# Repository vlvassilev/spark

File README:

spark-relay-actuator-pi is a hardware platform for managed power
distribution based on the Spark hardware platform
for networking. Both are developed by
Lightside Instruments AS.

The project includes schematic and PCB
design files for KiCAD and technical documentation for
production of a 19 inch rack mountable ESD Acrylic box.

The project is published by Lightside Instruments AS
under TAPR Open Hardware License. Read the LICENSE file
for details.

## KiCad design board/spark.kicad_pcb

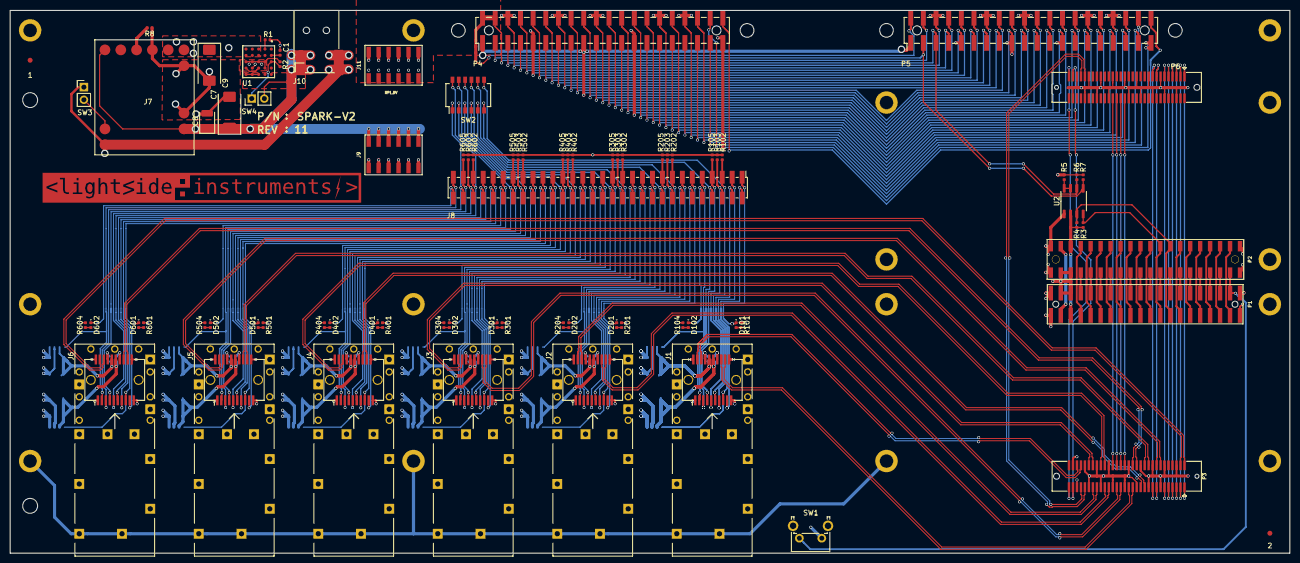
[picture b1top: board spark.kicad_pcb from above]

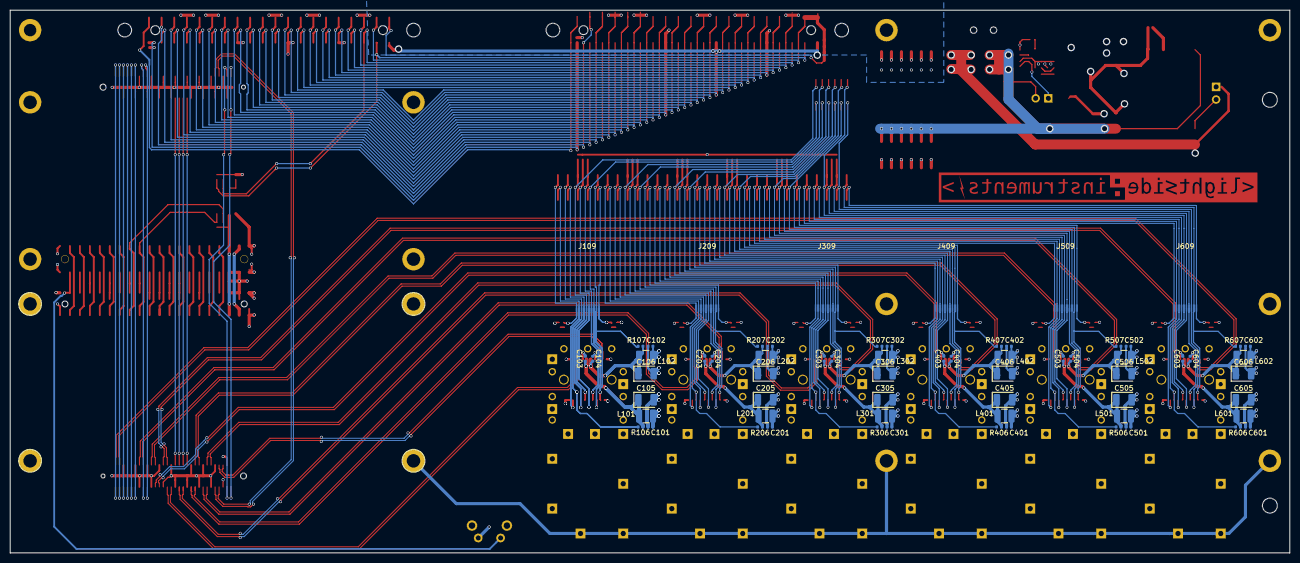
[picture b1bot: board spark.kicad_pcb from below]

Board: 4 copper layers, 257.0 x 109.0 mm, 145 parts (66 on the bottom side), 198 nets.

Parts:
1, 2: Fiducial_1mm_Mask3mm
C1: C; C_0402_1005Metric
C7: 330uF; CP_EIA-7343-31_Kemet-D
C8, C105, C106, C205, C206, C305, C306, C405, C406, C505, C506, C605, C606: 22uF; CP_EIA-3528-21_Kemet-B
C9: 220uF; CP_EIA-7343-31_Kemet-D
C101, C102, C103, C104, C201, C202, C203, C204, C301, C302, C303, C304, C401, C402, C403, C404, C501, C502, C503, C504, C601, C602, C603, C604: 100nF; C_0402_1005Metric
D101, D201, D301, D401, D501, D601: ADM_LED; LED_0402_1005Metric
D102, D202, D302, D402, D502, D602: ALARM_LED; LED_0402_1005Metric
J1, J2, J3, J4, J5, J6: SFP+; molex-sfp-plus-747540-101
J7: PTH08T221W; R-PDSS-B11
J8: Conn_02x30_Odd_Even; PinHeader_2x30_P2.00mm_Vertical_SMD
J9, J11: Conn_02x06_Odd_Even; Socket_Strip_SMD_2x6_Pitch2mm
J10: Barrel_Jack; PJ1-021-SMT-TR
J109, J209, J309, J409, J509, J609: Conn_01x10; sfp_header
L101, L102, L201, L202, L301, L302, L401, L402, L501, L502, L601, L602: 4.7uH; L_1210_3225Metric
P1: CONN_02X20; Pin_Header_SMD_2x20_Pitch2mm
P2: Conn_02x20_Odd_Even; Socket_Strip_SMD_2x20_Pitch2mm_Alignment_Pin
P3: CONN_02X30; 61083-063400LF
P4, P5: Conn_02x20_Odd_Even; PinSocket_2x20_P2.54mm_Vertical_Inverted_SMD_Alignment_Pin
P6: CONN_02X30; 5177983-2
R1: 13K3; C_0402_1005Metric
R2: 10K; C_0402_1005Metric
R3, R4, R6, R7: 4K7; R_0402_1005Metric
R5: 200K; R_0402_1005Metric
R8: 1K21; R_0402_1005Metric
R101, R104, R201, R204, R301, R304, R401, R404, R501, R504, R601, R604: 1K; R_0402_1005Metric
R102, R103, R105, R106, R107, R202, R203, R205, R206, R207, R302, R303, R305, R306, R307, R402, R403, R405, R406, R407, R502, R503, R505, R506, R507, R602, R603, R605, R606, R607: 10K; R_0402_1005Metric
SW1: SW_Push; SW_Tactile_SPST_Angled_PTS645Vx83-2LFS
SW2: SW_DIP_x06; SW_DIP_SPSTx06_Slide_Omron_A6H-6101_W6.15mm_P1.27mm
SW3, SW4: SW_DIP_x01; PinHeader_1x02_P2.54mm_Vertical
U1: LTM4624IYPBF; Analog_Devices_Inc-BGA-0-05-08-1905_Rev_C-0
U2: PCA9306; SO-8_3.9x4.9mm_P1.27mm

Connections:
+1V8: P1.35, P2.35, R3.1, R4.1, U2.2
+3V3: C9.1, C101.1, C102.1, C201.1, C202.1, C301.1, C302.1, C401.1, C402.1, C501.1, C502.1, C601.1, C602.1, J7.5, J7.6, L101.1, L102.1, L201.1, L202.1, L301.1, L302.1, L401.1, L402.1, L501.1, L502.1, L601.1, L602.1, P4.1, P4.17, P5.1, P5.17, R5.1, R6.1, R7.1, R101.1, R102.1, R103.1, R104.1, R105.1, R201.1, R202.1, R203.1, R204.1, R205.1, R301.1, R302.1, R303.1, R304.1, R305.1, R401.1, R402.1, R403.1, R404.1, R405.1, R501.1, R502.1, R503.1, R504.1, R505.1, R601.1, R602.1, R603.1, R604.1, R605.1, U1.C1, U1.D1, U1.D2, U1.E1, U1.E2
+5V: P1.37, P2.37
CHASSIS: J1.CAGE, J2.CAGE, J3.CAGE, J4.CAGE, J5.CAGE, J6.CAGE
CLK0/CSI0_MCLK: P3.15, P6.15
CLK1/CSI1_MCLK: P3.17, P6.17
CSI0_C+: J6.18, P3.2
CSI0_C-: J6.19, P3.4
CSI0_D1+: J5.18, P3.14
CSI0_D1-: J5.19, P3.16
CSI0_D2+: J5.13, P3.20
CSI0_D2-: J5.12, P3.22
CSI0_D3+: J6.13, P3.26
CSI0_D3-: J6.12, P3.28
CSI1_C+: J1.18, P3.54
CSI1_C-: J1.19, P3.56
CSI1_D0+: J4.18, P3.42
CSI1_D0-: J4.19, P3.44
CSI1_D1+: J3.18, P3.48
CSI1_D1-: J3.19, P3.50
DSI_CLK+: J4.13, P3.21
DSI_CLK-: J4.12, P3.23
DSI_D0+: J1.13, P3.27
DSI_D0-: J1.12, P3.29
DSI_D1+: J3.13, P3.33
DSI_D1-: J3.12, P3.35
DSI_D2+: J2.13, P3.39
DSI_D2-: J2.12, P3.41
DSI_D3+: J2.18, P3.45
DSI_D3-: J2.19, P3.47
GND: C1.2, C7.2, C8.2, C9.2, C101.2, C102.2, C103.2, C104.2, C105.2, C106.2, C201.2, C202.2, C203.2, C204.2, C205.2, C206.2, C301.2, C302.2, C303.2, C304.2, C305.2, C306.2, C401.2, C402.2, C403.2, C404.2, C405.2, C406.2, C501.2, C502.2, C503.2, C504.2, C505.2, C506.2, C601.2, C602.2, C603.2, C604.2, C605.2, C606.2, J1.1, J1.10, J1.11, J1.14, J1.17, J1.20, J2.1, J2.10, J2.11, J2.14, J2.17, J2.20, J3.1, J3.10, J3.11, J3.14, J3.17, J3.20, J4.1, J4.10, J4.11, J4.14, J4.17, J4.20, J5.1, J5.10, J5.11, J5.14, J5.17, J5.20, J6.1, J6.10, J6.11, J6.14, J6.17, J6.20, J7.1, J7.3, J7.4, J7.7, J9.1, J9.3, J9.5, J9.7, J9.9, J9.11, J10.2, J10.3, J11.2, J11.4, J11.6, J11.8, J11.10, J11.12, P1.1, P1.2, P1.39, P1.40, P2.1, P2.2, P2.39, P2.40, P3.6, P3.12, P3.13, P3.18, P3.19, P3.24, P3.25, P3.30, P3.31, P3.37, P3.40, P3.43, P3.46, P3.49, P3.52, P3.55, P3.58, P4.6, P4.9, P4.14, P4.20, P4.25, P4.30, P4.34, P4.39, P5.6, P5.9, P5.14, P5.20, P5.25, P5.30, P5.34, P5.39, P6.6, P6.12, P6.13, P6.18, P6.19, P6.24, P6.25, P6.30, P6.31, P6.37, P6.40, P6.43, P6.46, P6.49, P6.52, P6.55, P6.58, R1.2, R2.2, R8.1, SW1.1, SW3.1, U1.B3, U1.B4, U1.C3, U1.D3, U1.D4, U1.E3, U2.1
GPIO_A: P1.23, P2.23
GPIO_B: P1.24, P2.24
GPIO_C: P1.25, P2.25
GPIO_D: P1.26, P2.26
GPIO_E: P1.27, P2.27
GPIO_F: P1.28, P2.28
GPIO_G: P1.29, P2.29
GPIO_H: P1.30, P2.30
GPIO_I: P1.31, P2.31
GPIO_J: P1.32, P2.32
GPIO_K: P1.33, P2.33
GPIO_L: P1.34, P2.34
HSIC_DATA: P3.59, P6.59
HSIC_STR: P3.57, P6.57
I2C0_SCL: P1.15, P2.15, R4.2, U2.3
I2C0_SDA: P1.17, P2.17, R3.2, U2.4
I2C1_SCL: P1.19, P2.19
I2C1_SDA: P1.21, P2.21
I2C2_SCL: P3.32, P6.32
I2C2_SDA: P3.34, P6.34
I2C3_SCL: P3.36, P6.36
I2C3_SDA: P3.38, P6.38
unnamed: C1.1, U1.A2
unnamed: D101.2, R101.2
unnamed: D102.2, R104.2
unnamed: D201.2, R201.2
unnamed: D202.2, R204.2
unnamed: D301.2, R301.2
unnamed: D302.2, R304.2
unnamed: D401.2, R401.2
unnamed: D402.2, R404.2
unnamed: D501.2, R501.2
unnamed: D502.2, R504.2
unnamed: D601.2, R601.2
unnamed: D602.2, R604.2
unnamed: J7.8, R8.2
unnamed: J7.11, SW3.2
unnamed: P4.7, P5.7
unnamed: P4.8, P5.8
unnamed: P4.10, P5.10
unnamed: P4.11, P5.11
unnamed: P4.12, P5.12
unnamed: P4.13, P5.13
unnamed: P4.15, P5.15
unnamed: P4.16, P5.16
unnamed: P4.18, P5.18
unnamed: P4.19, P5.19
unnamed: P4.21, P5.21
unnamed: P4.22, P5.22
unnamed: P4.23, P5.23
unnamed: P4.24, P5.24
unnamed: P4.26, P5.26
unnamed: P4.27, P5.27
unnamed: P4.28, P5.28
unnamed: P4.29, P5.29
unnamed: P4.31, P5.31
unnamed: P4.32, P5.32
unnamed: P4.33, P5.33
unnamed: P4.35, P5.35
unnamed: P4.36, P5.36
unnamed: P4.37, P5.37
unnamed: P4.38, P5.38
unnamed: P4.40, P5.40
unnamed: R1.1, U1.B1
unnamed: R2.1, SW4.1, U1.A3
unnamed: R5.2, U2.7, U2.8
unnamed: U1.C4, U1.E4
PCM_CLK: P1.18, P2.18
PCM_DI: P1.22, P2.22
PCM_DO: P1.20, P2.20
PCM_FS: P1.16, P2.16
PWR_BTN_N: P1.4, P2.4, SW1.2
RPI_5V: J11.1, J11.3, J11.5, J11.7, J11.9, J11.11, P4.2, P4.4, P5.2, P5.4
RPI_I2C_SCL: P4.5, P5.5, R6.2, U2.6
RPI_I2C_SDA: P4.3, P5.3, R7.2, U2.5
RST_BTN_N: P1.6, P2.6
SD_CMD/SPI1_DIN: P3.11, P6.11
SD_DAT0/SPI1_DOUT: P3.1, P6.1
SD_DAT1: P3.3, P6.3
SD_DAT2: P3.5, P6.5
SD_DAT3/SPI1_CS: P3.7, P6.7
SD_SCLK/SPI1_SCLK: P3.9, P6.9
SFP0_ADM_LED: D101.1, J8.1, J109.1
SFP0_ALARM_LED: D102.1, J8.10, J109.10
SFP0_MOD_ABS: J1.6, J8.5, J109.5, R102.2, SW2.7
SFP0_RS0: J1.7, J8.4, J109.4
SFP0_RS1: J1.9, J8.2, J109.2
SFP0_RX_LOS: J1.8, J8.3, J109.3, R106.2
SFP0_SCL: J1.5, J8.6, J109.6, R103.2
SFP0_SDA: J1.4, J8.7, J109.7, R105.2
SFP0_TX_DISABLE: J1.3, J8.8, J109.8, SW2.6
SFP0_TX_FAULT: J1.2, J8.9, J109.9, R107.2
SFP0_VCC_R: C104.1, C106.1, J1.16, L102.2, R107.1
SFP0_VCC_T: C103.1, C105.1, J1.15, L101.2, R106.1
SFP1_ADM_LED: D201.1, J8.11, J209.1
SFP1_ALARM_LED: D202.1, J8.20, J209.10
SFP1_MOD_ABS: J2.6, J8.15, J209.5, R202.2, SW2.8
SFP1_RS0: J2.7, J8.14, J209.4
SFP1_RS1: J2.9, J8.12, J209.2
SFP1_RX_LOS: J2.8, J8.13, J209.3, R206.2
SFP1_SCL: J2.5, J8.16, J209.6, R203.2
SFP1_SDA: J2.4, J8.17, J209.7, R205.2
SFP1_TX_DISABLE: J2.3, J8.18, J209.8, SW2.5
SFP1_TX_FAULT: J2.2, J8.19, J209.9, R207.2
SFP1_VCC_R: C204.1, C206.1, J2.16, L202.2, R207.1
SFP1_VCC_T: C203.1, C205.1, J2.15, L201.2, R206.1
SFP2_ADM_LED: D301.1, J8.21, J309.1
SFP2_ALARM_LED: D302.1, J8.30, J309.10
SFP2_MOD_ABS: J3.6, J8.25, J309.5, R302.2, SW2.9
SFP2_RS0: J3.7, J8.24, J309.4
SFP2_RS1: J3.9, J8.22, J309.2
SFP2_RX_LOS: J3.8, J8.23, J309.3, R306.2
SFP2_SCL: J3.5, J8.26, J309.6, R303.2
SFP2_SDA: J3.4, J8.27, J309.7, R305.2
SFP2_TX_DISABLE: J3.3, J8.28, J309.8, SW2.4
SFP2_TX_FAULT: J3.2, J8.29, J309.9, R307.2
SFP2_VCC_R: C304.1, C306.1, J3.16, L302.2, R307.1
SFP2_VCC_T: C303.1, C305.1, J3.15, L301.2, R306.1
SFP3_ADM_LED: D401.1, J8.31, J409.1
SFP3_ALARM_LED: D402.1, J8.40, J409.10
SFP3_MOD_ABS: J4.6, J8.35, J409.5, R402.2, SW2.10
SFP3_RS0: J4.7, J8.34, J409.4
SFP3_RS1: J4.9, J8.32, J409.2
SFP3_RX_LOS: J4.8, J8.33, J409.3, R406.2
SFP3_SCL: J4.5, J8.36, J409.6, R403.2
SFP3_SDA: J4.4, J8.37, J409.7, R405.2
SFP3_TX_DISABLE: J4.3, J8.38, J409.8, SW2.3
SFP3_TX_FAULT: J4.2, J8.39, J409.9, R407.2
SFP3_VCC_R: C404.1, C406.1, J4.16, L402.2, R407.1
SFP3_VCC_T: C403.1, C405.1, J4.15, L401.2, R406.1
SFP4_ADM_LED: D501.1, J8.41, J509.1
SFP4_ALARM_LED: D502.1, J8.50, J509.10
SFP4_MOD_ABS: J5.6, J8.45, J509.5, R502.2, SW2.11
SFP4_RS0: J5.7, J8.44, J509.4
SFP4_RS1: J5.9, J8.42, J509.2
SFP4_RX_LOS: J5.8, J8.43, J509.3, R506.2
SFP4_SCL: J5.5, J8.46, J509.6, R503.2
SFP4_SDA: J5.4, J8.47, J509.7, R505.2
SFP4_TX_DISABLE: J5.3, J8.48, J509.8, SW2.2
SFP4_TX_FAULT: J5.2, J8.49, J509.9, R507.2
SFP4_VCC_R: C504.1, C506.1, J5.16, L502.2, R507.1
SFP4_VCC_T: C503.1, C505.1, J5.15, L501.2, R506.1
SFP5_ADM_LED: D601.1, J8.51, J609.1
SFP5_ALARM_LED: D602.1, J8.60, J609.10
SFP5_MOD_ABS: J6.6, J8.55, J609.5, R602.2, SW2.12
SFP5_RS0: J6.7, J8.54, J609.4
SFP5_RS1: J6.9, J8.52, J609.2
SFP5_RX_LOS: J6.8, J8.53, J609.3, R606.2
SFP5_SCL: J6.5, J8.56, J609.6, R603.2
SFP5_SDA: J6.4, J8.57, J609.7, R605.2
SFP5_TX_DISABLE: J6.3, J8.58, J609.8, SW2.1
SFP5_TX_FAULT: J6.2, J8.59, J609.9, R607.2
SFP5_VCC_R: C604.1, C606.1, J6.16, L602.2, R607.1
SFP5_VCC_T: C603.1, C605.1, J6.15, L601.2, R606.1
SPIO_CS: P1.12, P2.12
SPIO_DIN: P1.10, P2.10
SPIO_DOUT: P1.14, P2.14
SPIO_SCL: P1.8, P2.8
SYS_DCIN: C7.1, C8.1, J7.2, J7.10, J9.2, J9.4, J9.6, J9.8, J9.10, J9.12, J10.1, P1.36, P1.38, P2.36, P2.38, SW4.2, U1.C5, U1.D5, U1.E5
UART0_CTS: P1.3, P2.3
UART0_RTS: P1.9, P2.9
UART0_RX: P1.7, P2.7
UART0_TX: P1.5, P2.5
UART1_RX: P1.13, P2.13
UART1_TX: P1.11, P2.11
USB_D+: P3.51, P6.51
USB_D-: P3.53, P6.53

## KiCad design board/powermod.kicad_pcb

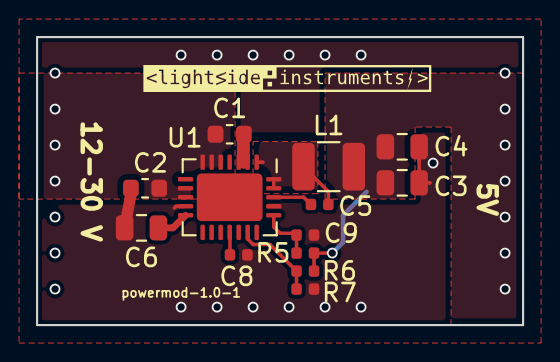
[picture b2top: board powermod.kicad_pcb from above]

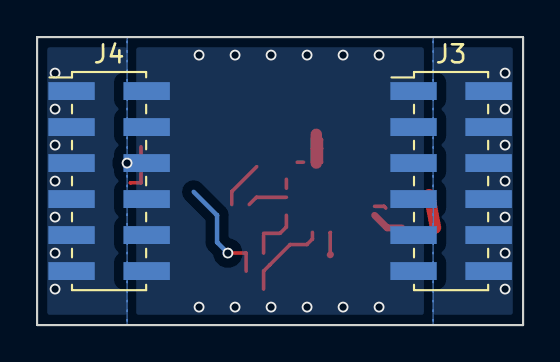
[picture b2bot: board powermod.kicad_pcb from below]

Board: 4 copper layers, 27.0 x 16.0 mm, 16 parts (2 on the bottom side), 9 nets.

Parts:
C1, C2: 2.2uF; C_0603_1608Metric
C3, C4: 22uF; C_0805_2012Metric
C5, C9: 0.1uF; C_0402_1005Metric
C6: 10uF; C_0805_2012Metric
C8: 22nF; C_0402_1005Metric
J3, J4: Conn_02x06_Odd_Even; PinHeader_2x06_P2.00mm_Vertical_SMD
L1: 10uH; L_1210_3225Metric
R5: 4.7K; R_0402_1005Metric
R6: 105K; R_0402_1005Metric
R7: 22.6K; R_0402_1005Metric
U1: MAX17574; QFN-24-1EP_4x5mm_P0.5mm_EP2.65x3.65mm
svg2mod: G***; lsi-logo-16mm

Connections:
+5V: C3.1, C4.1, J4.1, J4.3, J4.5, J4.7, J4.9, J4.11, L1.2, R5.1, R6.1
GND: C1.2, C2.2, C3.2, C4.2, C6.2, C8.2, C9.1, J3.1, J3.3, J3.5, J3.7, J3.9, J3.11, J4.2, J4.4, J4.6, J4.8, J4.10, J4.12, R7.2, U1.2, U1.3, U1.11, U1.21
unnamed: C5.1, L1.1, U1.1, U1.23, U1.24
unnamed: C5.2, U1.22
unnamed: C6.1, U1.12
unnamed: C8.1, U1.16
unnamed: C9.2, R5.2, U1.20
unnamed: R6.2, R7.1, U1.18
SYS_DCIN: C1.1, C2.1, J3.2, J3.4, J3.6, J3.8, J3.10, J3.12, U1.5, U1.6, U1.7, U1.9, U1.10

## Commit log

2019-11-02 Initial release
2020-06-12 Release 1.0
2020-07-16 Release 2.0
2020-08-18 Release 2.0-2
2020-10-28 Release 2.0-3
2021-01-29 Release 2.0-4
2021-02-07 Release 2.0-5
2021-02-19 Release 2.0-6
2021-02-20 Release 2.0-7
2021-06-04 Release 2.0-8
2021-06-04 Release 2.0-9
2021-08-26 spark-pdu-1.0-1
2021-11-22 spark-pdu-pi-1.0-1
2021-12-03 spark-pdu-pi-1-2
2021-12-05 Release 2.0-10
2021-12-20 spark-pdu-pi-1-3
2021-12-20 spark-pdu-pi-1-4
2021-12-25 spark-relay-actuator-pi-1-1
2021-12-26 spark-relay-actuator-pi-1-2
2021-12-26 spark-relay-actuator-pi-1-3
2021-12-30 spark-relay-actuator-pi-2-1
2021-12-31 Release 2.0-11
2022-01-26 spark-relay-actuator-pi-2-2
2022-05-04 Added initial extras/cabrio-holder
2022-05-05 Added 4 hole vertical and horizontal lego technics compatible beams and the missing openscad file
